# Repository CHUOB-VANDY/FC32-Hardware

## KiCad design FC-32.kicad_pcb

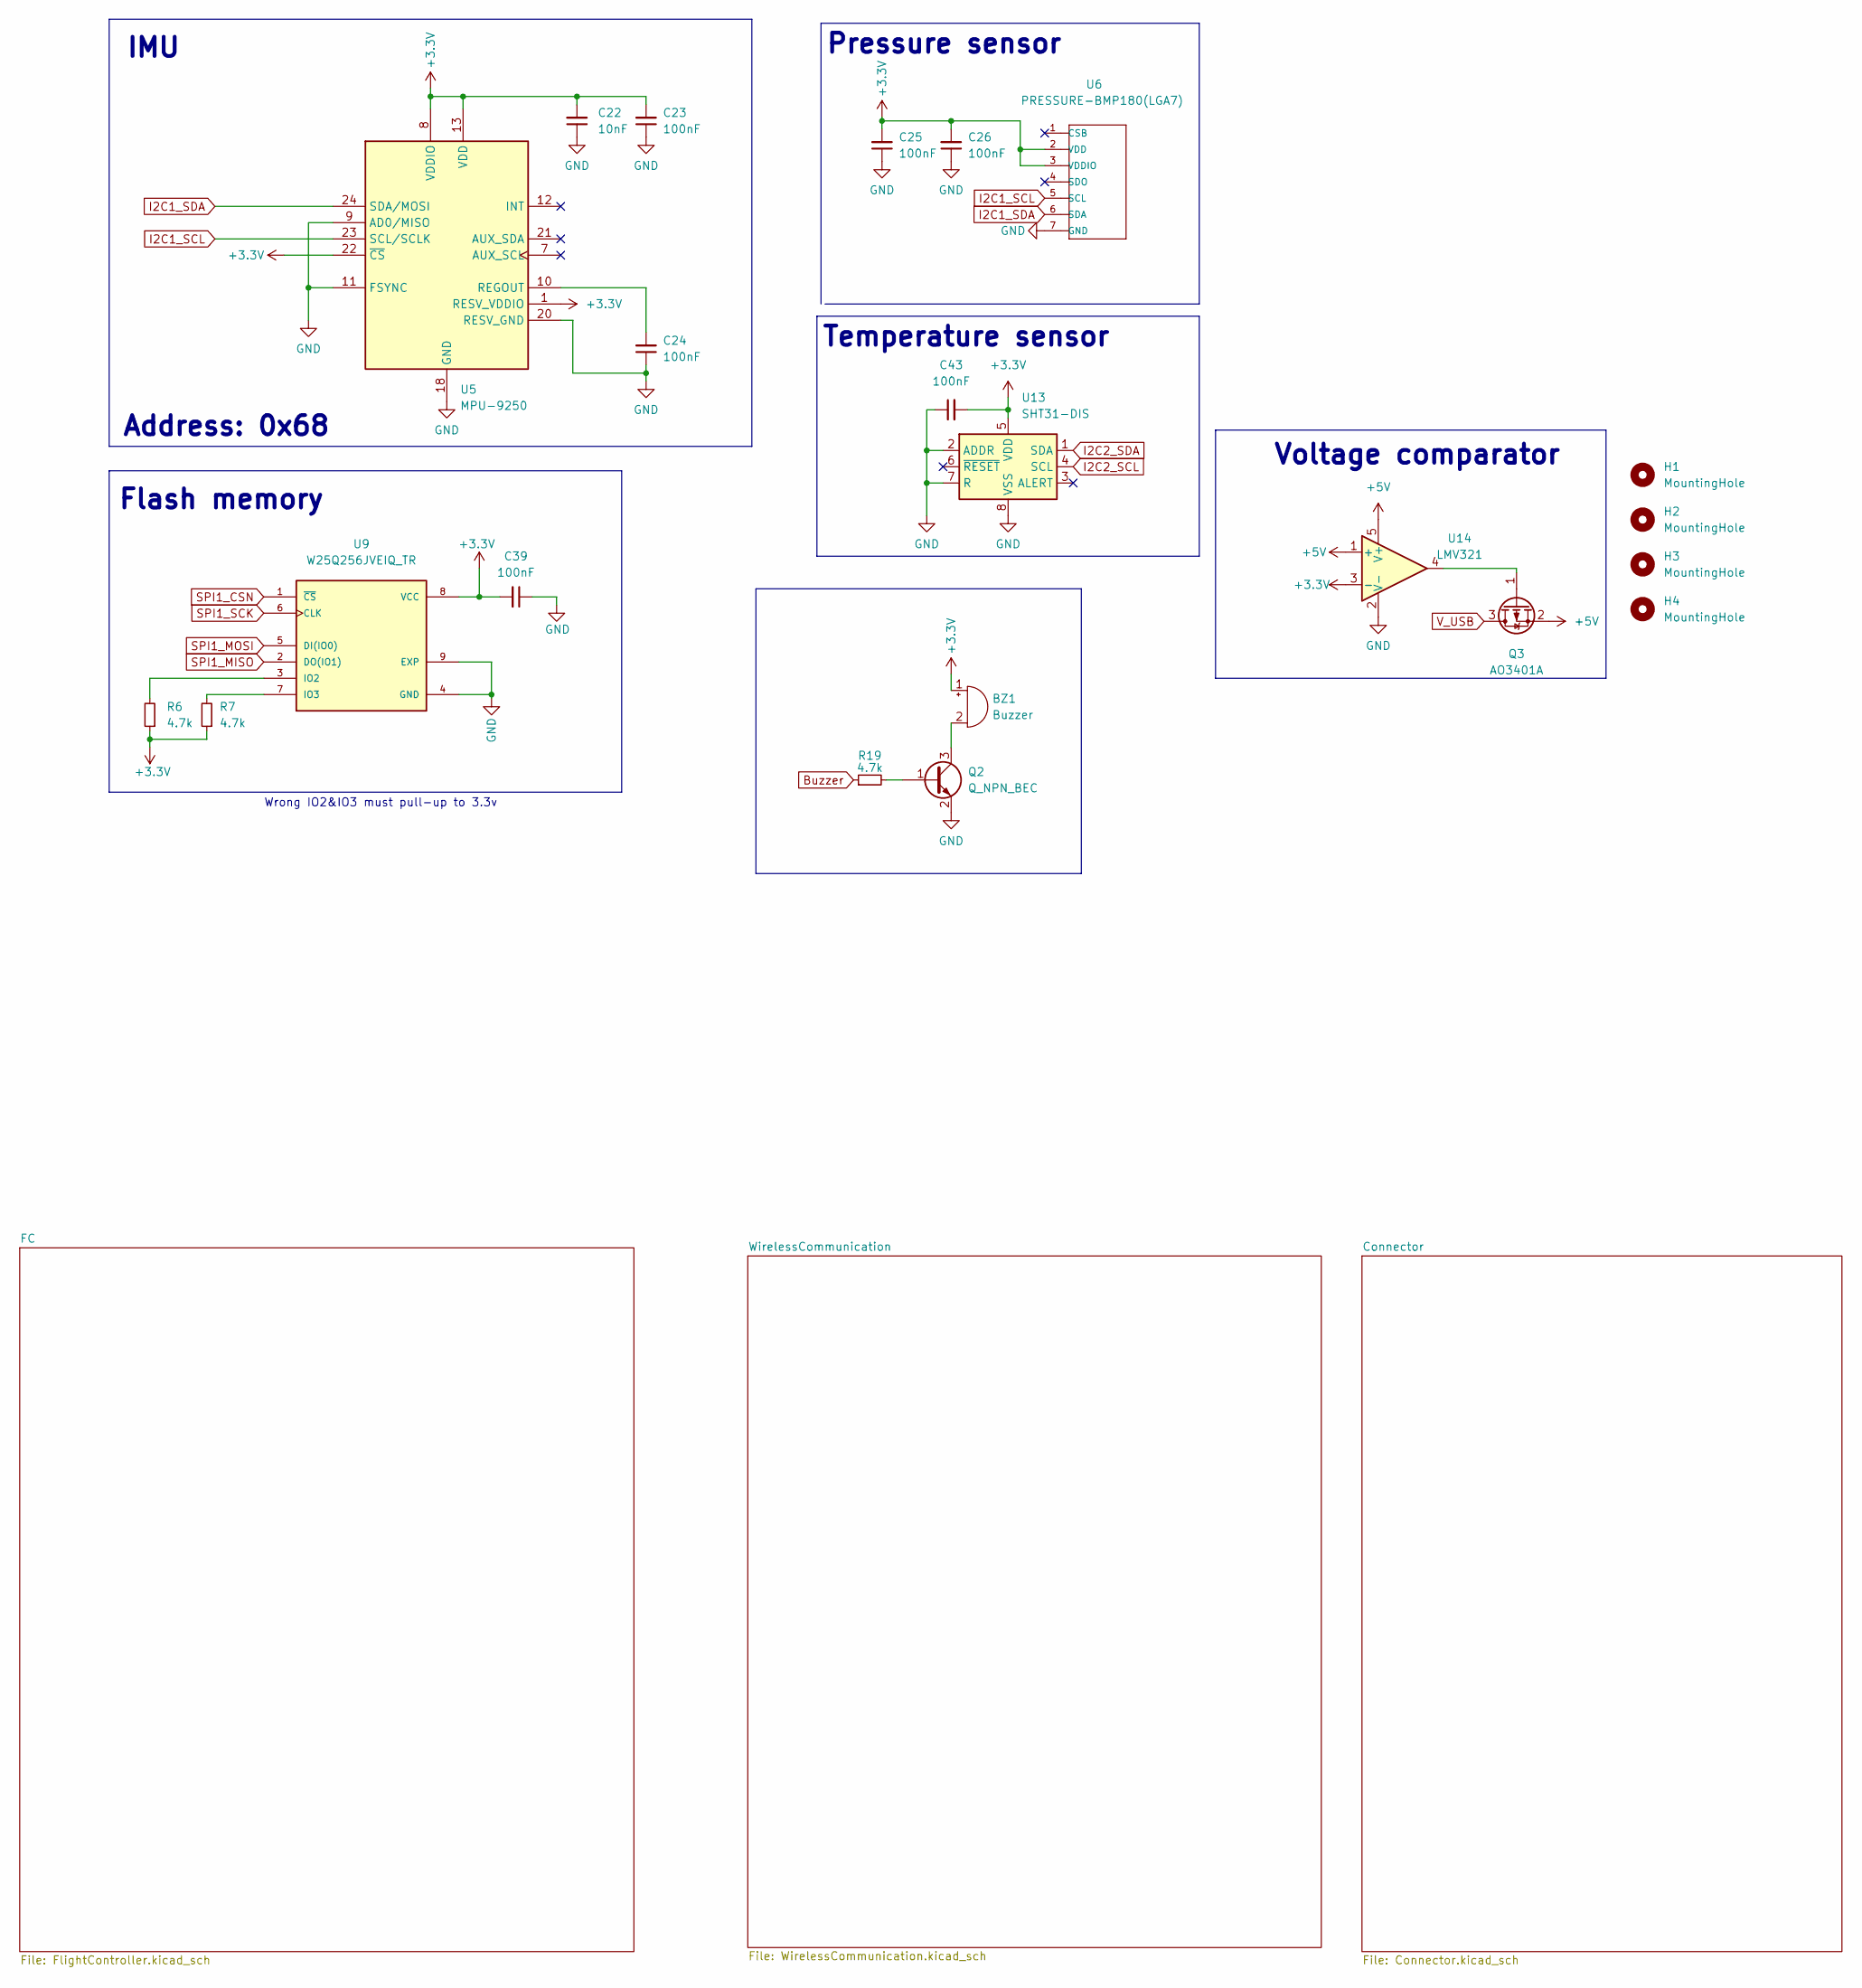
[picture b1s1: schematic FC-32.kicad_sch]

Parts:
BZ1: Buzzer; Buzzer_12x9.5RM7.6
C22: 10nF; C_0603_1608Metric
C23, C24, C25, C26, C39, C43: 100nF; C_0603_1608Metric
H1, H2, H3, H4: MountingHole; MountingHole_3mm_Pad_Via
Q2: Q_NPN_BEC; SOT-23
Q3: AO3401A; SOT-23
R6, R7, R19: 4.7k; R_0603_1608Metric
U5: MPU-9250; InvenSense_QFN-24_3x3mm_P0.4mm
U6: PRESSURE-BMP180(LGA7); LGA7-1.5-3.8X3.6MM; MPN BMP18
U9: W25Q256JVEIQ_TR; SON127P800X600X80-9N
U13: SHT31-DIS; Sensirion_DFN-8-1EP_2.5x2.5mm_P0.5mm_EP1.1x1.7mm
U14: LMV321; SOT-23-5

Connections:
+3V3: BZ1.1 (-), C22.2, C23.2, C25.2, C26.2, C39.2, C43.2, R6.1, R7.1, U5.1 (RESV_VDDIO), U5.8 (VDDIO), U5.13 (VDD), U5.22 (~CS), U6.2 (VDD), U6.3 (VDDIO), U9.8 (VCC), U13.5 (VDD), U14.3 (-); also elsewhere on the board
+5V: Q3.2 (S), U14.1 (+), U14.5 (V+); also elsewhere on the board
Buzzer: R19.1; also elsewhere on the board
GND: C22.1, C23.1, C24.1, C25.1, C26.1, C39.1, C43.1, Q2.2 (E), U5.9 (AD0/MISO), U5.11 (FSYNC), U5.18 (GND), U5.20 (RESV_GND), U6.7 (GND), U9.4 (GND), U9.9 (EXP), U13.2 (ADDR), U13.7 (R), U13.8 (VSS), U13.9 (VSS), U14.2 (V-); also elsewhere on the board
I2C1_SCL: U5.23 (SCL/SCLK), U6.5 (SCL); also elsewhere on the board
I2C1_SDA: U5.24 (SDA/MOSI), U6.6 (SDA); also elsewhere on the board
I2C2_SCL: U13.4 (SCL); also elsewhere on the board
I2C2_SDA: U13.1 (SDA); also elsewhere on the board
unnamed: BZ1.2 (+), Q2.3 (C)
unnamed: C24.2, U5.10 (REGOUT)
unnamed: Q2.1 (B), R19.2
unnamed: Q3.1 (G), U14.4
unnamed: R6.2, U9.3 (IO2)
unnamed: R7.2, U9.7 (IO3)
SPI1_CSN: U9.1 (~CS); also elsewhere on the board
SPI1_MISO: U9.2 (DO(IO1)); also elsewhere on the board
SPI1_MOSI: U9.5 (DI(IO0)); also elsewhere on the board
SPI1_SCK: U9.6 (CLK); also elsewhere on the board
V_USB: Q3.3 (D); also elsewhere on the board

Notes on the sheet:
Address: 0x68
Voltage comparator
Pressure sensor
Wrong IO2&IO3 must pull-up to 3.3v
Temperature sensor
IMU
Flash memory

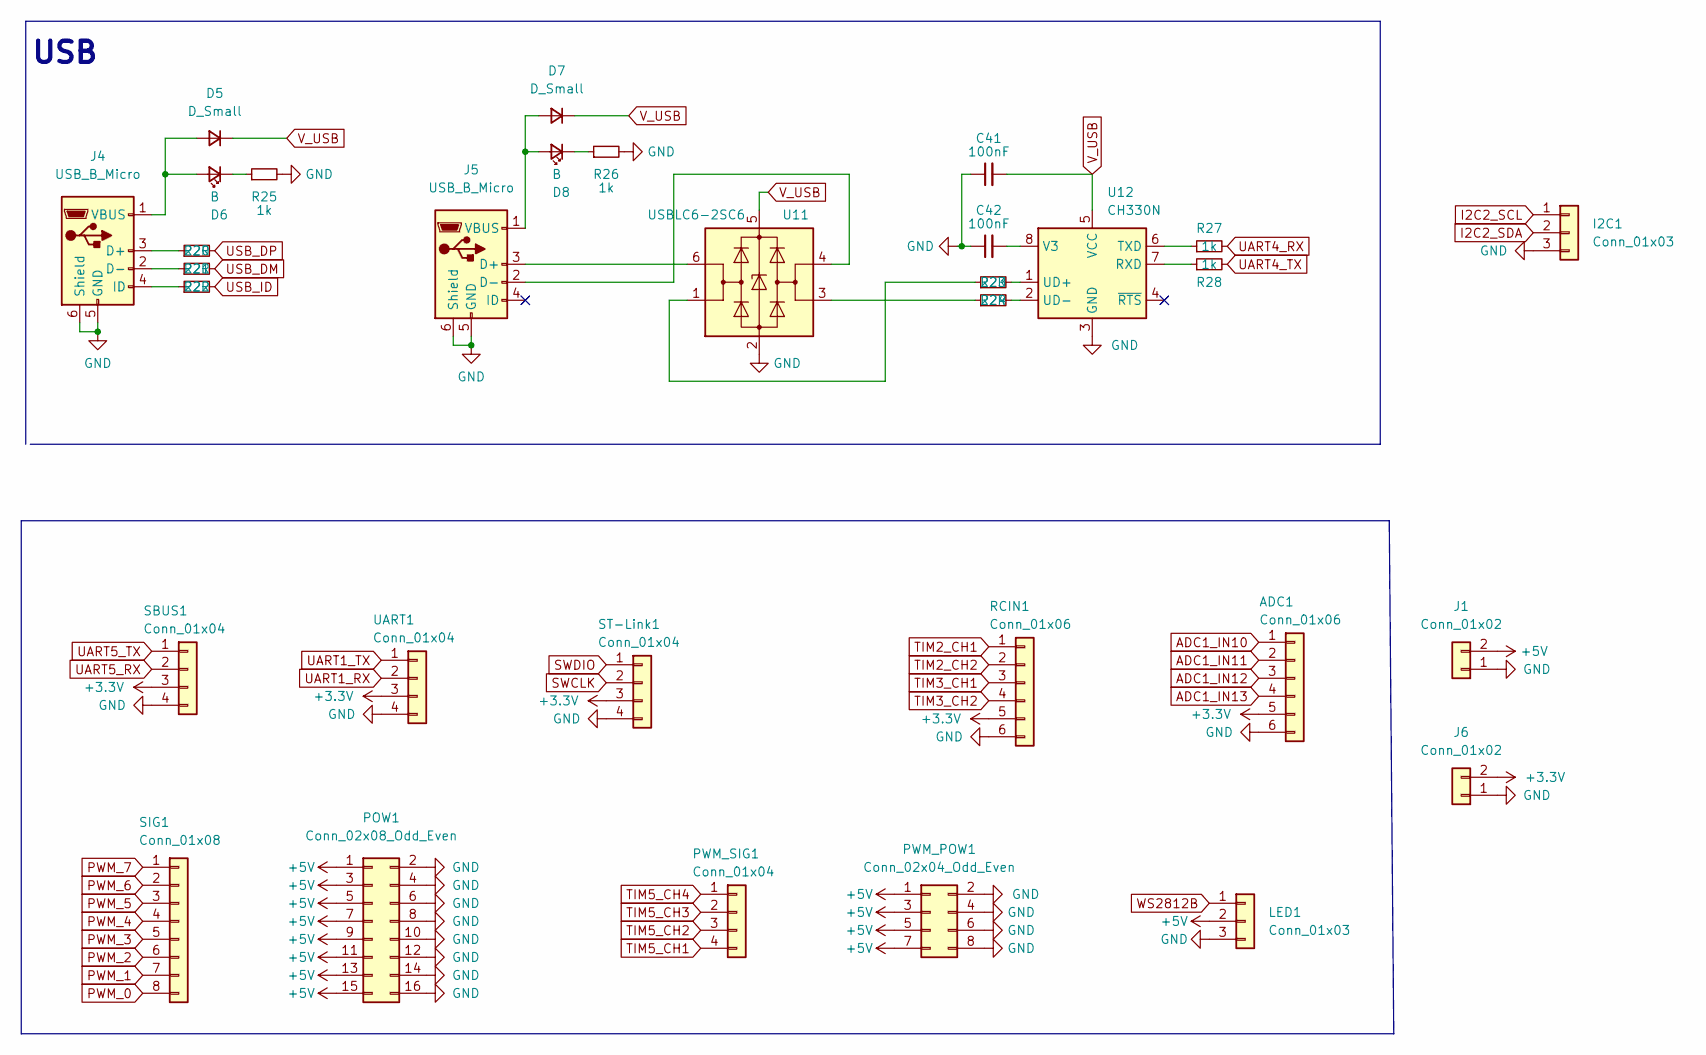
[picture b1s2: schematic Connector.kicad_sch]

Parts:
ADC1: Conn_01x06; Molex_CLIK-Mate_502494-0670_1x06-1MP_P2.00mm_Horizontal
C41, C42: 100nF; C_0603_1608Metric
D5, D7: D_Small; D_SMA
D6, D8: B; LED_0603_1608Metric
I2C1: Conn_01x03; ConPadx03
J1, J6: Conn_01x02; Molex_CLIK-Mate_502494-0270_1x02-1MP_P2.00mm_Horizontal
J4, J5: USB_B_Micro; USB_Micro-B_Molex-105017-0001
LED1: Conn_01x03; Molex_CLIK-Mate_502494-0370_1x03-1MP_P2.00mm_Horizontal
POW1: Conn_02x08_Odd_Even; PinHeader_2x08_P2.54mm_Vertical
PWM_POW1: Conn_02x04_Odd_Even; PinHeader_2x04_P2.54mm_Vertical
PWM_SIG1: Conn_01x04; PinHeader_1x04_P2.54mm_Vertical
R20, R21, R22, R23, R24: 22R; R_0603_1608Metric
R25, R26, R27, R28: 1k; R_0603_1608Metric
RCIN1: Conn_01x06; Molex_CLIK-Mate_502494-0670_1x06-1MP_P2.00mm_Horizontal
SBUS1: Conn_01x04; Molex_CLIK-Mate_502494-0470_1x04-1MP_P2.00mm_Horizontal
SIG1: Conn_01x08; PinHeader_1x08_P2.54mm_Vertical
ST-Link1: Conn_01x04; Molex_CLIK-Mate_502494-0470_1x04-1MP_P2.00mm_Horizontal
U11: USBLC6-2SC6; SOT-23-6
U12: CH330N; SOIC-8_3.9x4.9mm_P1.27mm
UART1: Conn_01x04; Molex_CLIK-Mate_502494-0470_1x04-1MP_P2.00mm_Horizontal

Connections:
+3V3: ADC1.5, J6.2, RCIN1.5, SBUS1.3, ST-Link1.3, UART1.3; also elsewhere on the board
+5V: J1.2, LED1.2, POW1.1, POW1.3, POW1.5, POW1.7, POW1.9, POW1.11, POW1.13, POW1.15, PWM_POW1.1, PWM_POW1.3, PWM_POW1.5, PWM_POW1.7; also elsewhere on the board
ADC1_IN10: ADC1.1; also elsewhere on the board
ADC1_IN11: ADC1.2; also elsewhere on the board
ADC1_IN12: ADC1.3; also elsewhere on the board
ADC1_IN13: ADC1.4; also elsewhere on the board
GND: ADC1.6, C41.1, C42.1, I2C1.3, J1.1, J4.5 (GND), J4.6 (Shield), J5.5 (GND), J5.6 (Shield), J6.1, LED1.3, POW1.2, POW1.4, POW1.6, POW1.8, POW1.10, POW1.12, POW1.14, POW1.16, PWM_POW1.2, PWM_POW1.4, PWM_POW1.6, PWM_POW1.8, R25.2, R26.2, RCIN1.6, SBUS1.4, ST-Link1.4, U11.2 (GND), U12.3 (GND), UART1.4; also elsewhere on the board
I2C2_SCL: I2C1.1; also elsewhere on the board
I2C2_SDA: I2C1.2; also elsewhere on the board
unnamed: C42.2, U12.8 (V3)
unnamed: D5.2 (A), D6.2 (A), J4.1 (VBUS)
unnamed: D6.1 (K), R25.1
unnamed: D7.2 (A), D8.2 (A), J5.1 (VBUS)
unnamed: D8.1 (K), R26.1
unnamed: J4.2 (D-), R21.1
unnamed: J4.3 (D+), R20.1
unnamed: J4.4 (ID), R22.1
unnamed: J5.2 (D-), U11.4 (I/O2)
unnamed: J5.3 (D+), U11.6 (I/O1)
unnamed: R23.1, U11.1 (I/O1)
unnamed: R23.2, U12.1 (UD+)
unnamed: R24.1, U11.3 (I/O2)
unnamed: R24.2, U12.2 (UD-)
unnamed: R27.1, U12.6 (TXD)
unnamed: R28.1, U12.7 (RXD)
PWM_0: SIG1.8; also elsewhere on the board
PWM_1: SIG1.7; also elsewhere on the board
PWM_2: SIG1.6; also elsewhere on the board
PWM_3: SIG1.5; also elsewhere on the board
PWM_4: SIG1.4; also elsewhere on the board
PWM_5: SIG1.3; also elsewhere on the board
PWM_6: SIG1.2; also elsewhere on the board
PWM_7: SIG1.1; also elsewhere on the board
SWCLK: ST-Link1.2; also elsewhere on the board
SWDIO: ST-Link1.1; also elsewhere on the board
TIM2_CH1: RCIN1.1; also elsewhere on the board
TIM2_CH2: RCIN1.2; also elsewhere on the board
TIM3_CH1: RCIN1.3; also elsewhere on the board
TIM3_CH2: RCIN1.4; also elsewhere on the board
TIM5_CH1: PWM_SIG1.4; also elsewhere on the board
TIM5_CH2: PWM_SIG1.3; also elsewhere on the board
TIM5_CH3: PWM_SIG1.2; also elsewhere on the board
TIM5_CH4: PWM_SIG1.1; also elsewhere on the board
UART1_RX: UART1.2; also elsewhere on the board
UART1_TX: UART1.1; also elsewhere on the board
UART4_RX: R27.2; also elsewhere on the board
UART4_TX: R28.2; also elsewhere on the board
UART5_RX: SBUS1.2; also elsewhere on the board
UART5_TX: SBUS1.1; also elsewhere on the board
USB_DM: R21.2; also elsewhere on the board
USB_DP: R20.2; also elsewhere on the board
USB_ID: R22.2; also elsewhere on the board
V_USB: C41.2, D5.1 (K), D7.1 (K), U11.5 (VBUS), U12.5 (VCC); also elsewhere on the board
WS2812B: LED1.1; also elsewhere on the board

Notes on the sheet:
USB

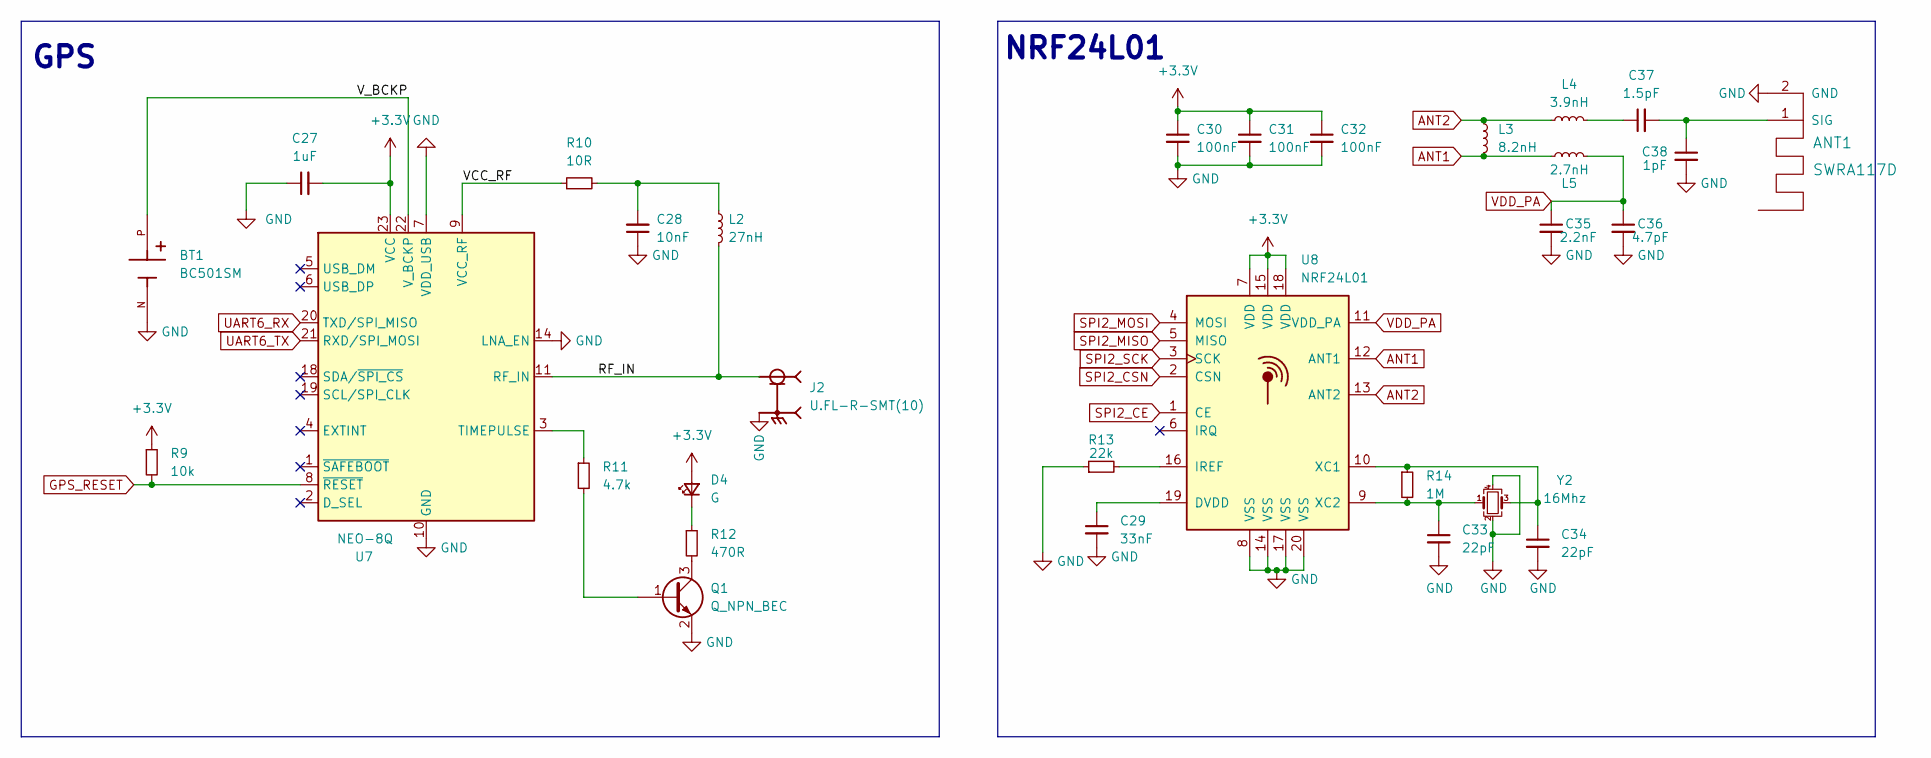
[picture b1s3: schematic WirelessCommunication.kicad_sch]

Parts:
ANT1: SWRA117D; Texas_SWRA117D_2.4GHz_Left
BT1: BC501SM; BAT_BC501SM; PARTREV 10/31/19
C27: 1uF; C_0603_1608Metric
C28: 10nF; C_0603_1608Metric
C29: 33nF; C_0603_1608Metric
C30, C31, C32: 100nF; C_0603_1608Metric
C33, C34: 22pF; C_0603_1608Metric
C35: 2.2nF; C_0603_1608Metric
C36: 4.7pF; C_0603_1608Metric
C37: 1.5pF; C_0603_1608Metric
C38: 1pF; C_0603_1608Metric
D4: G; LED_0603_1608Metric
J2: U.FL-R-SMT(10); HRS_U.FL-R-SMT(10)
L2: 27nH; L_0603_1608Metric
L3: 8.2nH; L_0603_1608Metric
L4: 3.9nH; L_0603_1608Metric
L5: 2.7nH; L_0603_1608Metric
Q1: Q_NPN_BEC; SOT-23
R9: 10k; R_0603_1608Metric
R10: 10R; R_0603_1608Metric
R11: 4.7k; R_0603_1608Metric
R12: 470R; R_0603_1608Metric
R13: 22k; R_0603_1608Metric
R14: 1M; R_0603_1608Metric
U7: NEO-8Q; ublox_NEO
U8: NRF24L01; QFN-20-1EP_4x4mm_P0.5mm_EP2.5x2.5mm
Y2: 16Mhz; Crystal_SMD_3225-4Pin_3.2x2.5mm

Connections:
+3V3: C27.2, C30.1, C31.1, C32.1, D4.2 (A), R9.1, U7.23 (VCC), U8.7 (VDD), U8.15 (VDD), U8.18 (VDD); also elsewhere on the board
/WirelessCommunication/RF_IN: J2.1, L2.2, U7.11 (RF_IN)
/WirelessCommunication/VCC_RF: R10.1, U7.9 (VCC_RF)
/WirelessCommunication/V_BCKP: BT1.P, U7.22 (V_BCKP)
ANT1: L3.2, L5.1, U8.12 (ANT1)
ANT2: L3.1, L4.1, U8.13 (ANT2)
GND: ANT1.2 (GND), BT1.N, C27.1, C28.1, C29.2, C30.2, C31.2, C32.2, C33.2, C34.2, C35.2, C36.2, C38.2, J2.2, J2.3, Q1.2 (E), R13.1, U7.7 (VDD_USB), U7.10 (GND), U7.12 (GND), U7.13 (GND), U7.14 (LNA_EN), U7.24 (GND), U8.8 (VSS), U8.14 (VSS), U8.17 (VSS), U8.20 (VSS), Y2.2, Y2.4; also elsewhere on the board
GPS_RESET: R9.2, U7.8 (~RESET); also elsewhere on the board
unnamed: ANT1.1 (SIG), C37.2, C38.1
unnamed: C28.2, L2.1, R10.2
unnamed: C29.1, U8.19 (DVDD)
unnamed: C33.1, R14.2, U8.9 (XC2), Y2.1
unnamed: C34.1, R14.1, U8.10 (XC1), Y2.3
unnamed: C37.1, L4.2
unnamed: D4.1 (K), R12.1
unnamed: Q1.1 (B), R11.2
unnamed: Q1.3 (C), R12.2
unnamed: R11.1, U7.3 (TIMEPULSE)
unnamed: R13.2, U8.16 (IREF)
SPI2_CE: U8.1 (CE); also elsewhere on the board
SPI2_CSN: U8.2 (CSN); also elsewhere on the board
SPI2_MISO: U8.5 (MISO); also elsewhere on the board
SPI2_MOSI: U8.4 (MOSI); also elsewhere on the board
SPI2_SCK: U8.3 (SCK); also elsewhere on the board
UART6_RX: U7.20 (TXD/SPI_MISO); also elsewhere on the board
UART6_TX: U7.21 (RXD/SPI_MOSI); also elsewhere on the board
VDD_PA: C35.1, C36.1, L5.2, U8.11 (VDD_PA)

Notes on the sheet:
GPS
NRF24L01

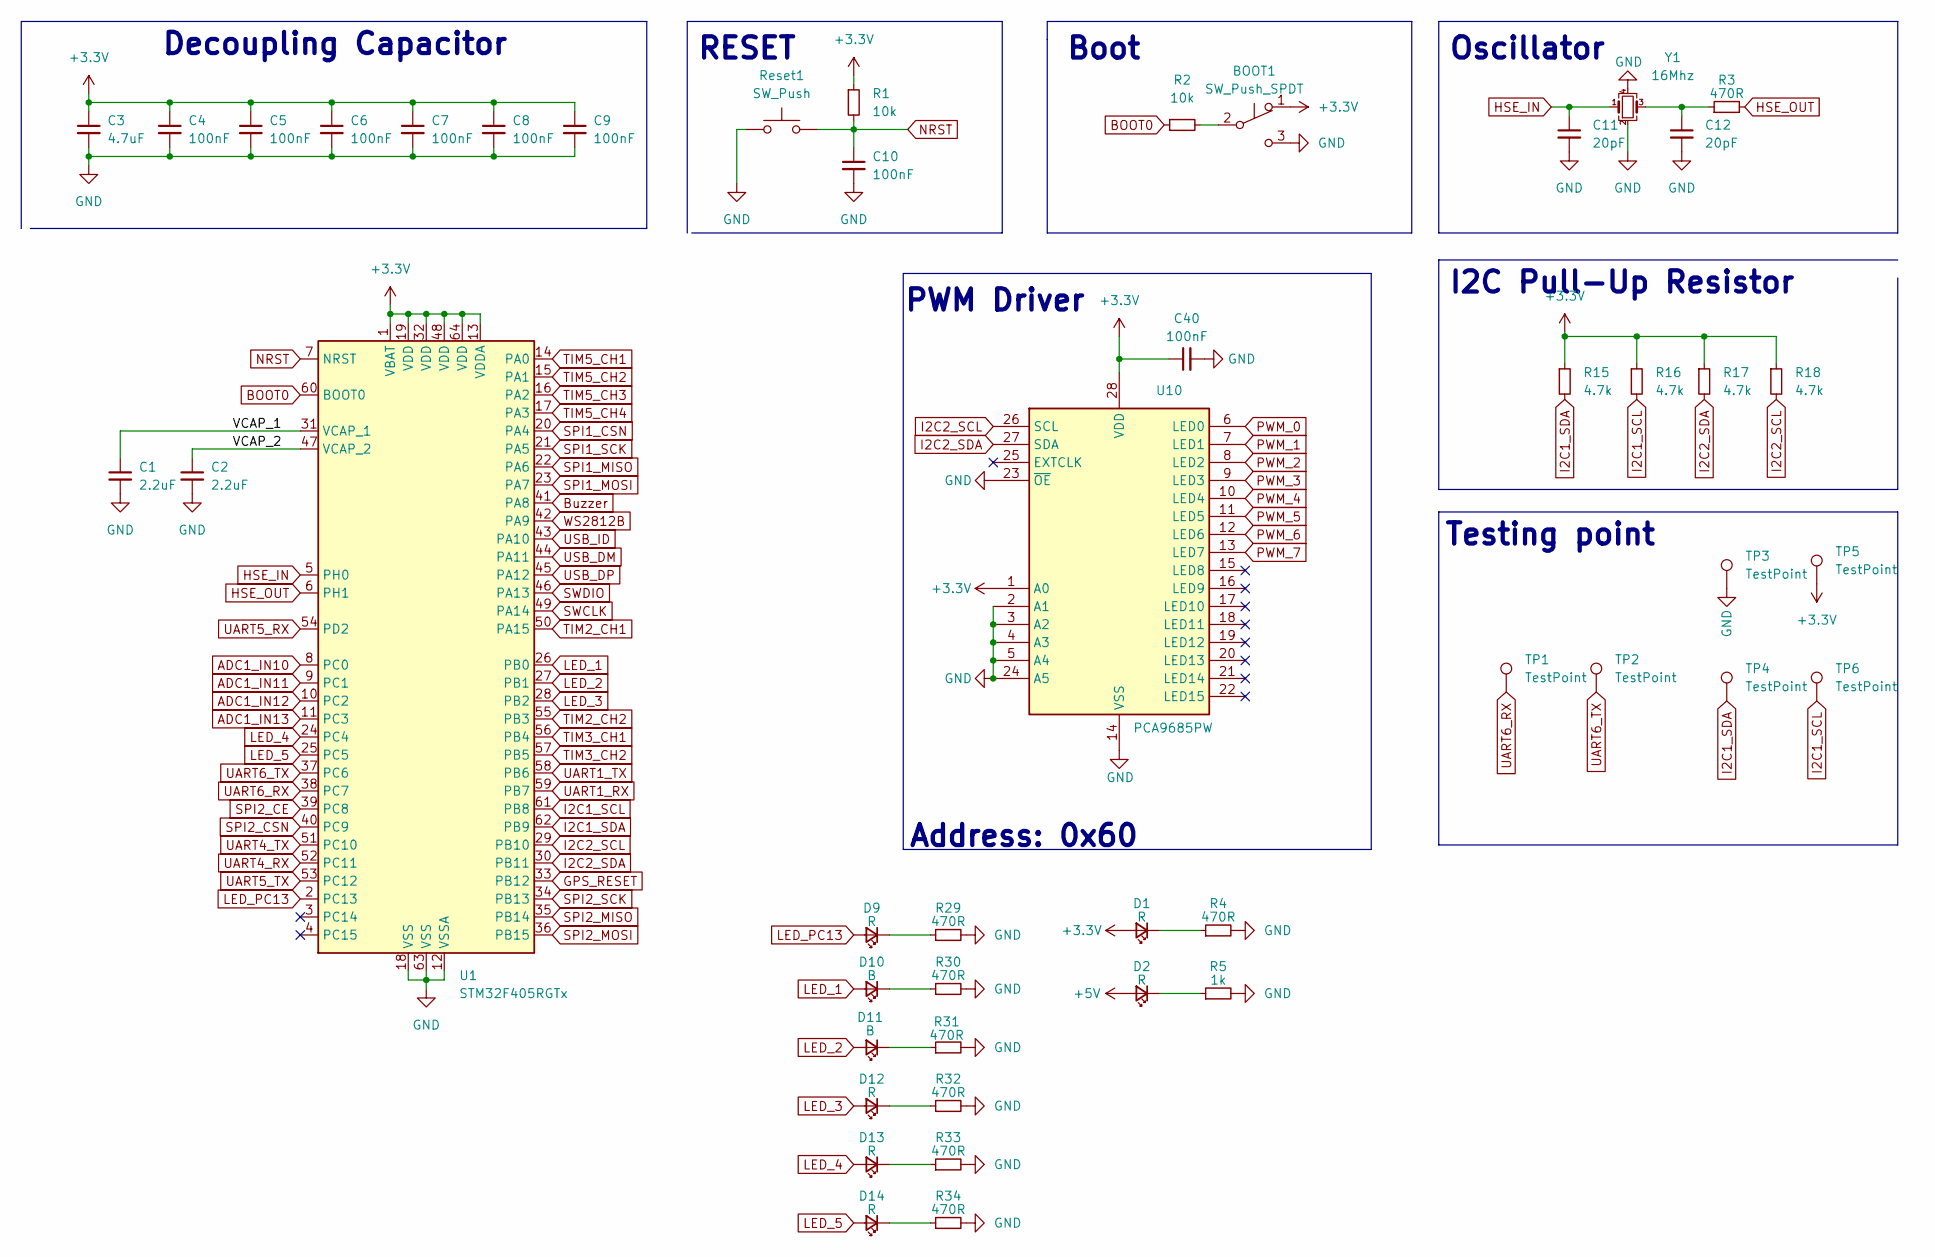
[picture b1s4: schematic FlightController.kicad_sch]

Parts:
BOOT1: SW_Push_SPDT; SW_SPDT_PCM12
C1, C2: 2.2uF; C_0603_1608Metric
C3: 4.7uF; C_0805_2012Metric
C4, C5, C6, C7, C8, C9, C10, C40: 100nF; C_0603_1608Metric
C11, C12: 20pF; C_0603_1608Metric
D1, D2, D9, D12, D13, D14: R; LED_0603_1608Metric
D10, D11: B; LED_0603_1608Metric
R1, R2: 10k; R_0603_1608Metric
R3, R4, R29, R30, R31, R32, R33, R34: 470R; R_0603_1608Metric
R5: 1k; R_0603_1608Metric
R15, R16, R17, R18: 4.7k; R_0603_1608Metric
Reset1: SW_Push; SW_SPST_TL3342
TP1, TP2, TP3, TP4, TP5, TP6: TestPoint; TestPoint_Pad_D1.0mm
U1: STM32F405RGTx; LQFP-64_10x10mm_P0.5mm
U10: PCA9685PW; TSSOP-28_4.4x9.7mm_P0.65mm
Y1: 16Mhz; Crystal_SMD_3225-4Pin_3.2x2.5mm

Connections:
+3V3: BOOT1.1 (A), C3.1, C4.1, C5.1, C6.1, C7.1, C8.1, C9.1, C40.1, D1.2 (A), R1.1, R15.1, R16.1, R17.1, R18.1, TP5.1, U1.1 (VBAT), U1.13 (VDDA), U1.19 (VDD), U1.32 (VDD), U1.48 (VDD), U1.64 (VDD), U10.1 (A0), U10.28 (VDD); also elsewhere on the board
+5V: D2.2 (A); also elsewhere on the board
/FC/VCAP_1: C1.1, U1.31 (VCAP_1)
/FC/VCAP_2: C2.1, U1.47 (VCAP_2)
ADC1_IN10: U1.8 (PC0); also elsewhere on the board
ADC1_IN11: U1.9 (PC1); also elsewhere on the board
ADC1_IN12: U1.10 (PC2); also elsewhere on the board
ADC1_IN13: U1.11 (PC3); also elsewhere on the board
BOOT0: R2.1, U1.60 (BOOT0)
Buzzer: U1.41 (PA8); also elsewhere on the board
GND: BOOT1.3 (C), C1.2, C2.2, C3.2, C4.2, C5.2, C6.2, C7.2, C8.2, C9.2, C10.2, C11.2, C12.2, C40.2, R4.2, R5.2, R29.2, R30.2, R31.2, R32.2, R33.2, R34.2, Reset1.1, TP3.1, U1.12 (VSSA), U1.18 (VSS), U1.63 (VSS), U10.2 (A1), U10.3 (A2), U10.4 (A3), U10.5 (A4), U10.14 (VSS), U10.23 (~OE), U10.24 (A5), Y1.2, Y1.4; also elsewhere on the board
GPS_RESET: U1.33 (PB12); also elsewhere on the board
HSE_IN: C11.1, U1.5 (PH0), Y1.1
HSE_OUT: R3.2, U1.6 (PH1)
I2C1_SCL: R16.2, TP6.1, U1.61 (PB8); also elsewhere on the board
I2C1_SDA: R15.2, TP4.1, U1.62 (PB9); also elsewhere on the board
I2C2_SCL: R18.2, U1.29 (PB10), U10.26 (SCL); also elsewhere on the board
I2C2_SDA: R17.2, U1.30 (PB11), U10.27 (SDA); also elsewhere on the board
LED_1: D10.2 (A), U1.26 (PB0)
LED_2: D11.2 (A), U1.27 (PB1)
LED_3: D12.2 (A), U1.28 (PB2)
LED_4: D13.2 (A), U1.24 (PC4)
LED_5: D14.2 (A), U1.25 (PC5)
LED_PC13: D9.2 (A), U1.2 (PC13)
NRST: C10.1, R1.2, Reset1.2, U1.7 (NRST)
unnamed: BOOT1.2 (B), R2.2
unnamed: C12.1, R3.1, Y1.3
unnamed: D1.1 (K), R4.1
unnamed: D2.1 (K), R5.1
unnamed: D9.1 (K), R29.1
unnamed: D10.1 (K), R30.1
unnamed: D11.1 (K), R31.1
unnamed: D12.1 (K), R32.1
unnamed: D13.1 (K), R33.1
unnamed: D14.1 (K), R34.1
PWM_0: U10.6 (LED0); also elsewhere on the board
PWM_1: U10.7 (LED1); also elsewhere on the board
PWM_2: U10.8 (LED2); also elsewhere on the board
PWM_3: U10.9 (LED3); also elsewhere on the board
PWM_4: U10.10 (LED4); also elsewhere on the board
PWM_5: U10.11 (LED5); also elsewhere on the board
PWM_6: U10.12 (LED6); also elsewhere on the board
PWM_7: U10.13 (LED7); also elsewhere on the board
SPI1_CSN: U1.20 (PA4); also elsewhere on the board
SPI1_MISO: U1.22 (PA6); also elsewhere on the board
SPI1_MOSI: U1.23 (PA7); also elsewhere on the board
SPI1_SCK: U1.21 (PA5); also elsewhere on the board
SPI2_CE: U1.39 (PC8); also elsewhere on the board
SPI2_CSN: U1.40 (PC9); also elsewhere on the board
SPI2_MISO: U1.35 (PB14); also elsewhere on the board
SPI2_MOSI: U1.36 (PB15); also elsewhere on the board
SPI2_SCK: U1.34 (PB13); also elsewhere on the board
SWCLK: U1.49 (PA14); also elsewhere on the board
SWDIO: U1.46 (PA13); also elsewhere on the board
TIM2_CH1: U1.50 (PA15); also elsewhere on the board
TIM2_CH2: U1.55 (PB3); also elsewhere on the board
TIM3_CH1: U1.56 (PB4); also elsewhere on the board
TIM3_CH2: U1.57 (PB5); also elsewhere on the board
TIM5_CH1: U1.14 (PA0); also elsewhere on the board
TIM5_CH2: U1.15 (PA1); also elsewhere on the board
TIM5_CH3: U1.16 (PA2); also elsewhere on the board
TIM5_CH4: U1.17 (PA3); also elsewhere on the board
UART1_RX: U1.59 (PB7); also elsewhere on the board
UART1_TX: U1.58 (PB6); also elsewhere on the board
UART4_RX: U1.52 (PC11); also elsewhere on the board
UART4_TX: U1.51 (PC10); also elsewhere on the board
UART5_RX: U1.54 (PD2); also elsewhere on the board
UART5_TX: U1.53 (PC12); also elsewhere on the board
UART6_RX: TP1.1, U1.38 (PC7); also elsewhere on the board
UART6_TX: TP2.1, U1.37 (PC6); also elsewhere on the board
USB_DM: U1.44 (PA11); also elsewhere on the board
USB_DP: U1.45 (PA12); also elsewhere on the board
USB_ID: U1.43 (PA10); also elsewhere on the board
WS2812B: U1.42 (PA9); also elsewhere on the board

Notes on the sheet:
Testing point
Boot
I2C Pull-Up Resistor
Decoupling Capacitor
Address: 0x60
PWM Driver
Oscillator
RESET

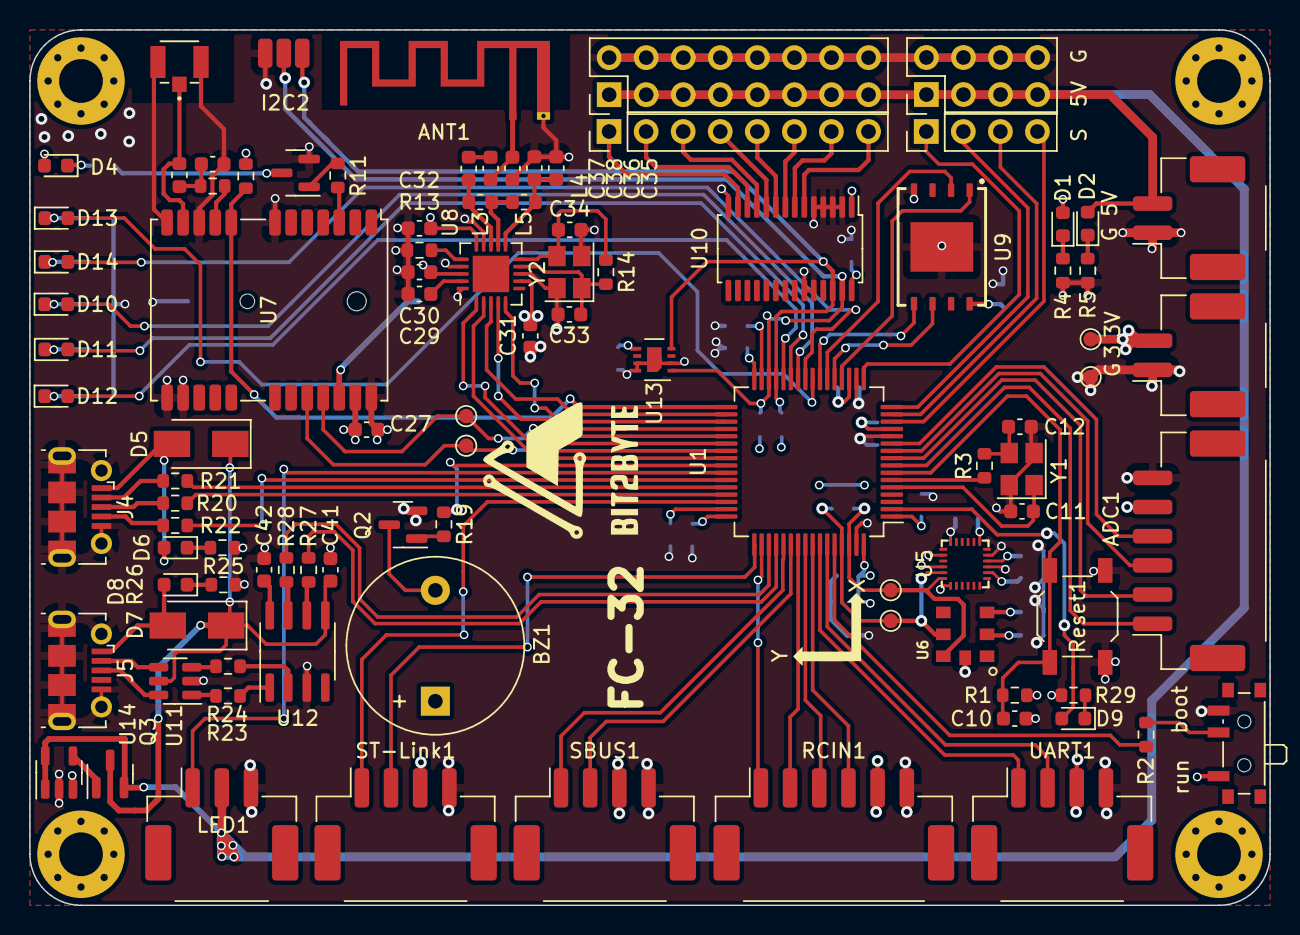
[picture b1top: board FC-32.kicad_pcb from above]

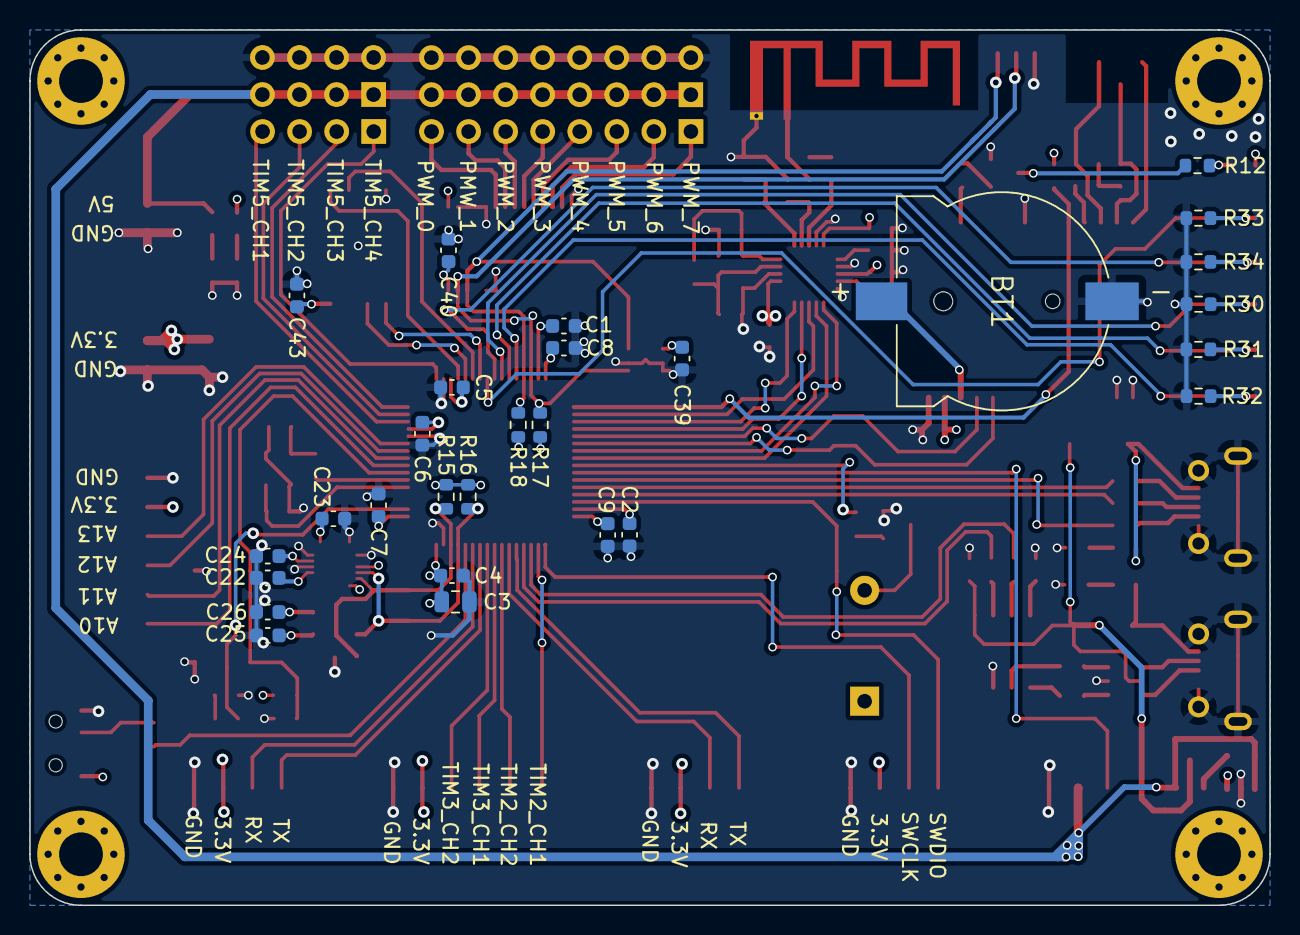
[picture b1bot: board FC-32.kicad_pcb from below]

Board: 4 copper layers, 85.0 x 60.0 mm, 129 parts (28 on the bottom side), 112 nets.
